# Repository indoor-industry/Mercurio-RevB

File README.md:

Requires CDFER's KiCAD library (https://github.com/CDFER/JLCPCB-Kicad-Library) and the custom symbol and footprint libraries in Component models/KiCAD_symbol_ library. 

Contains version with bare ESP32-S3R8 chip and version with ESP32-WROOM-1 module. Only major difference is bare chip version features RTC clock and uses strapping pin GPIO46 for ILI9341 DC line. This should work but has to be tested.

## License

See the [LICENSE](LICENSE) file for details.

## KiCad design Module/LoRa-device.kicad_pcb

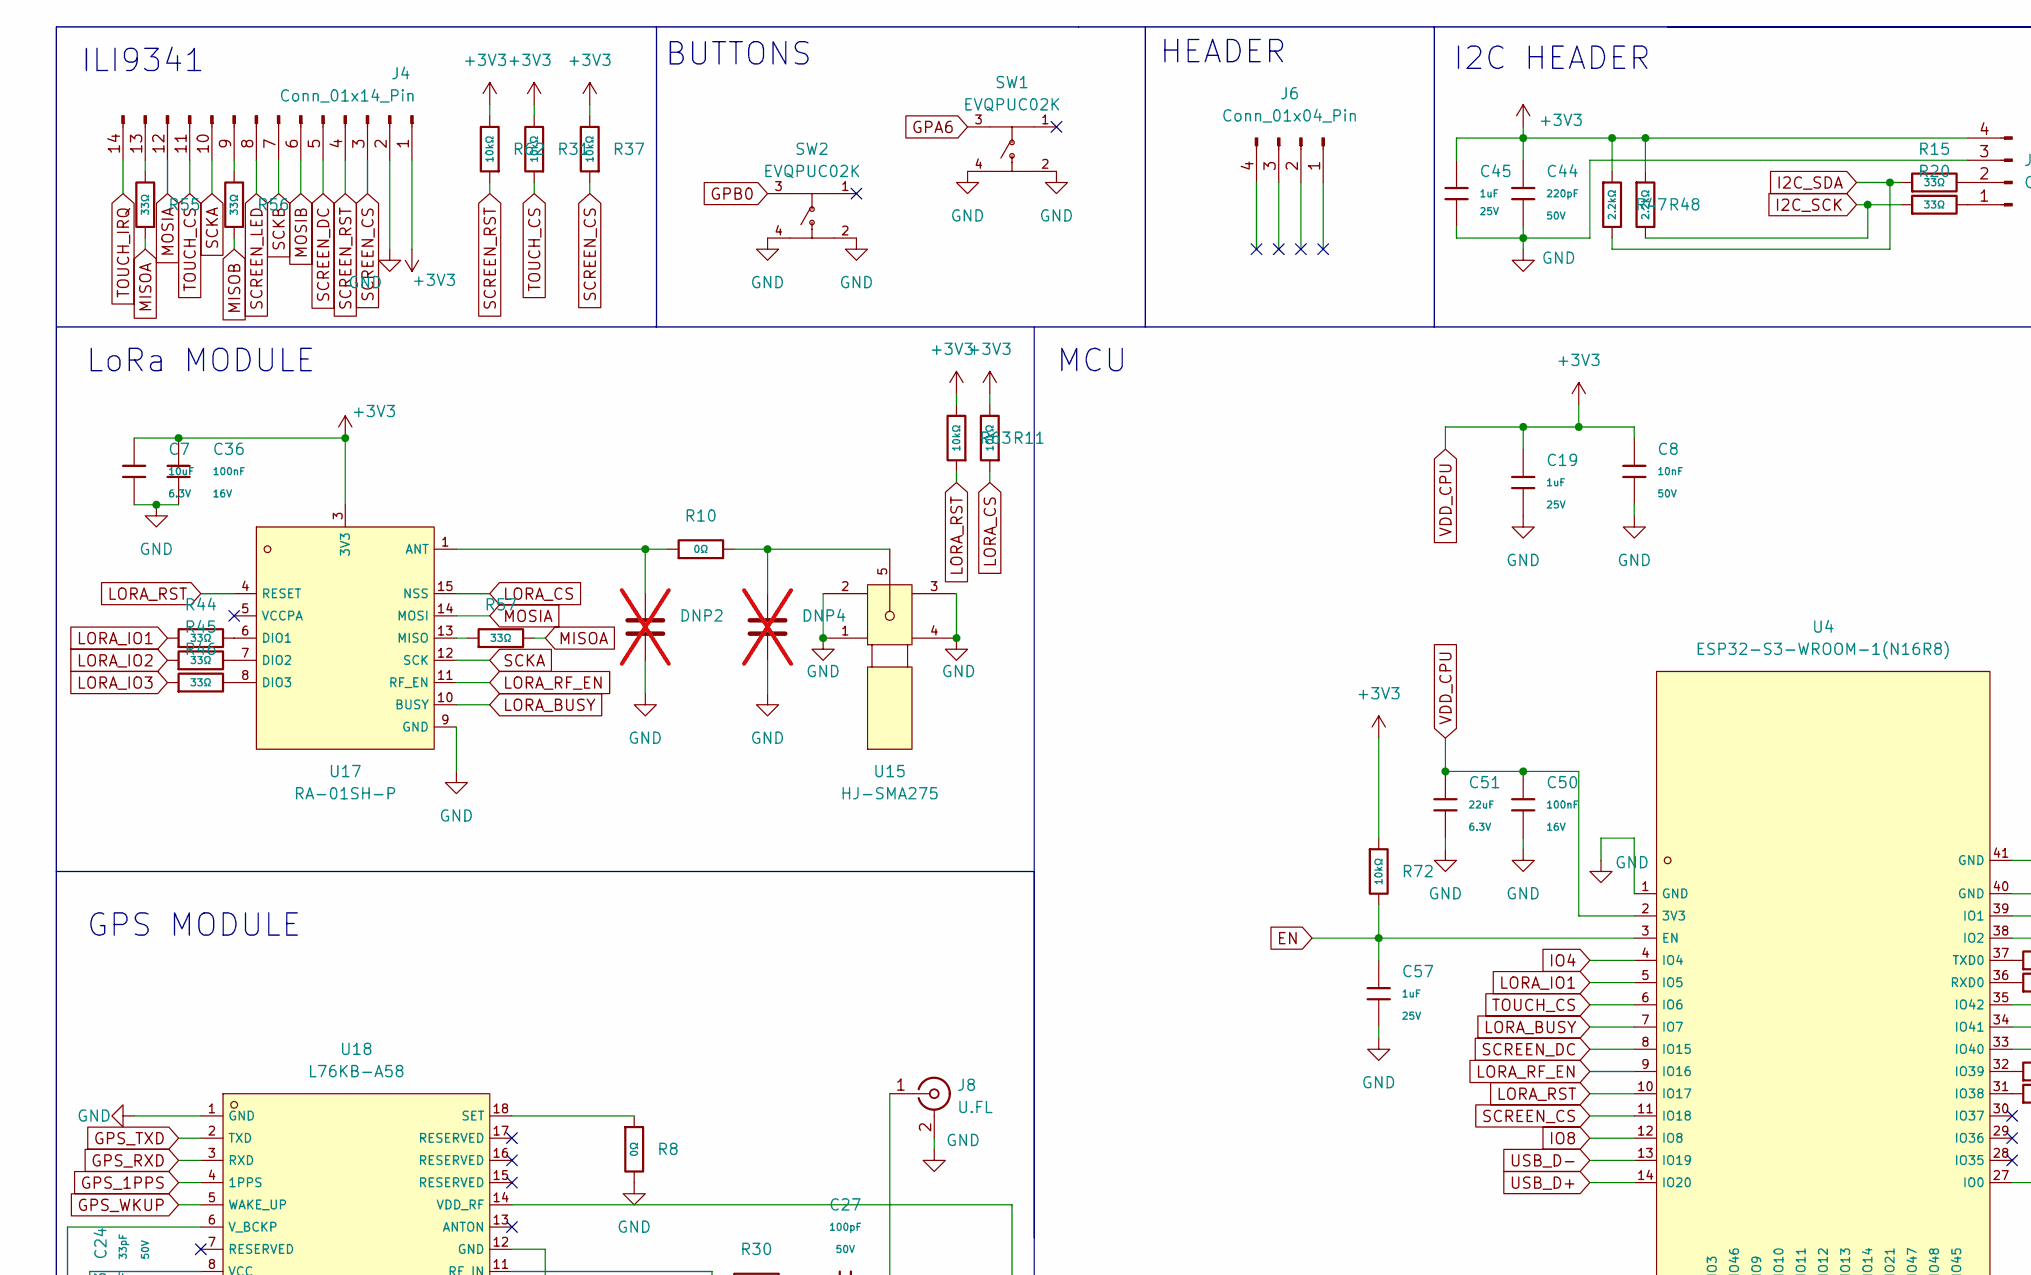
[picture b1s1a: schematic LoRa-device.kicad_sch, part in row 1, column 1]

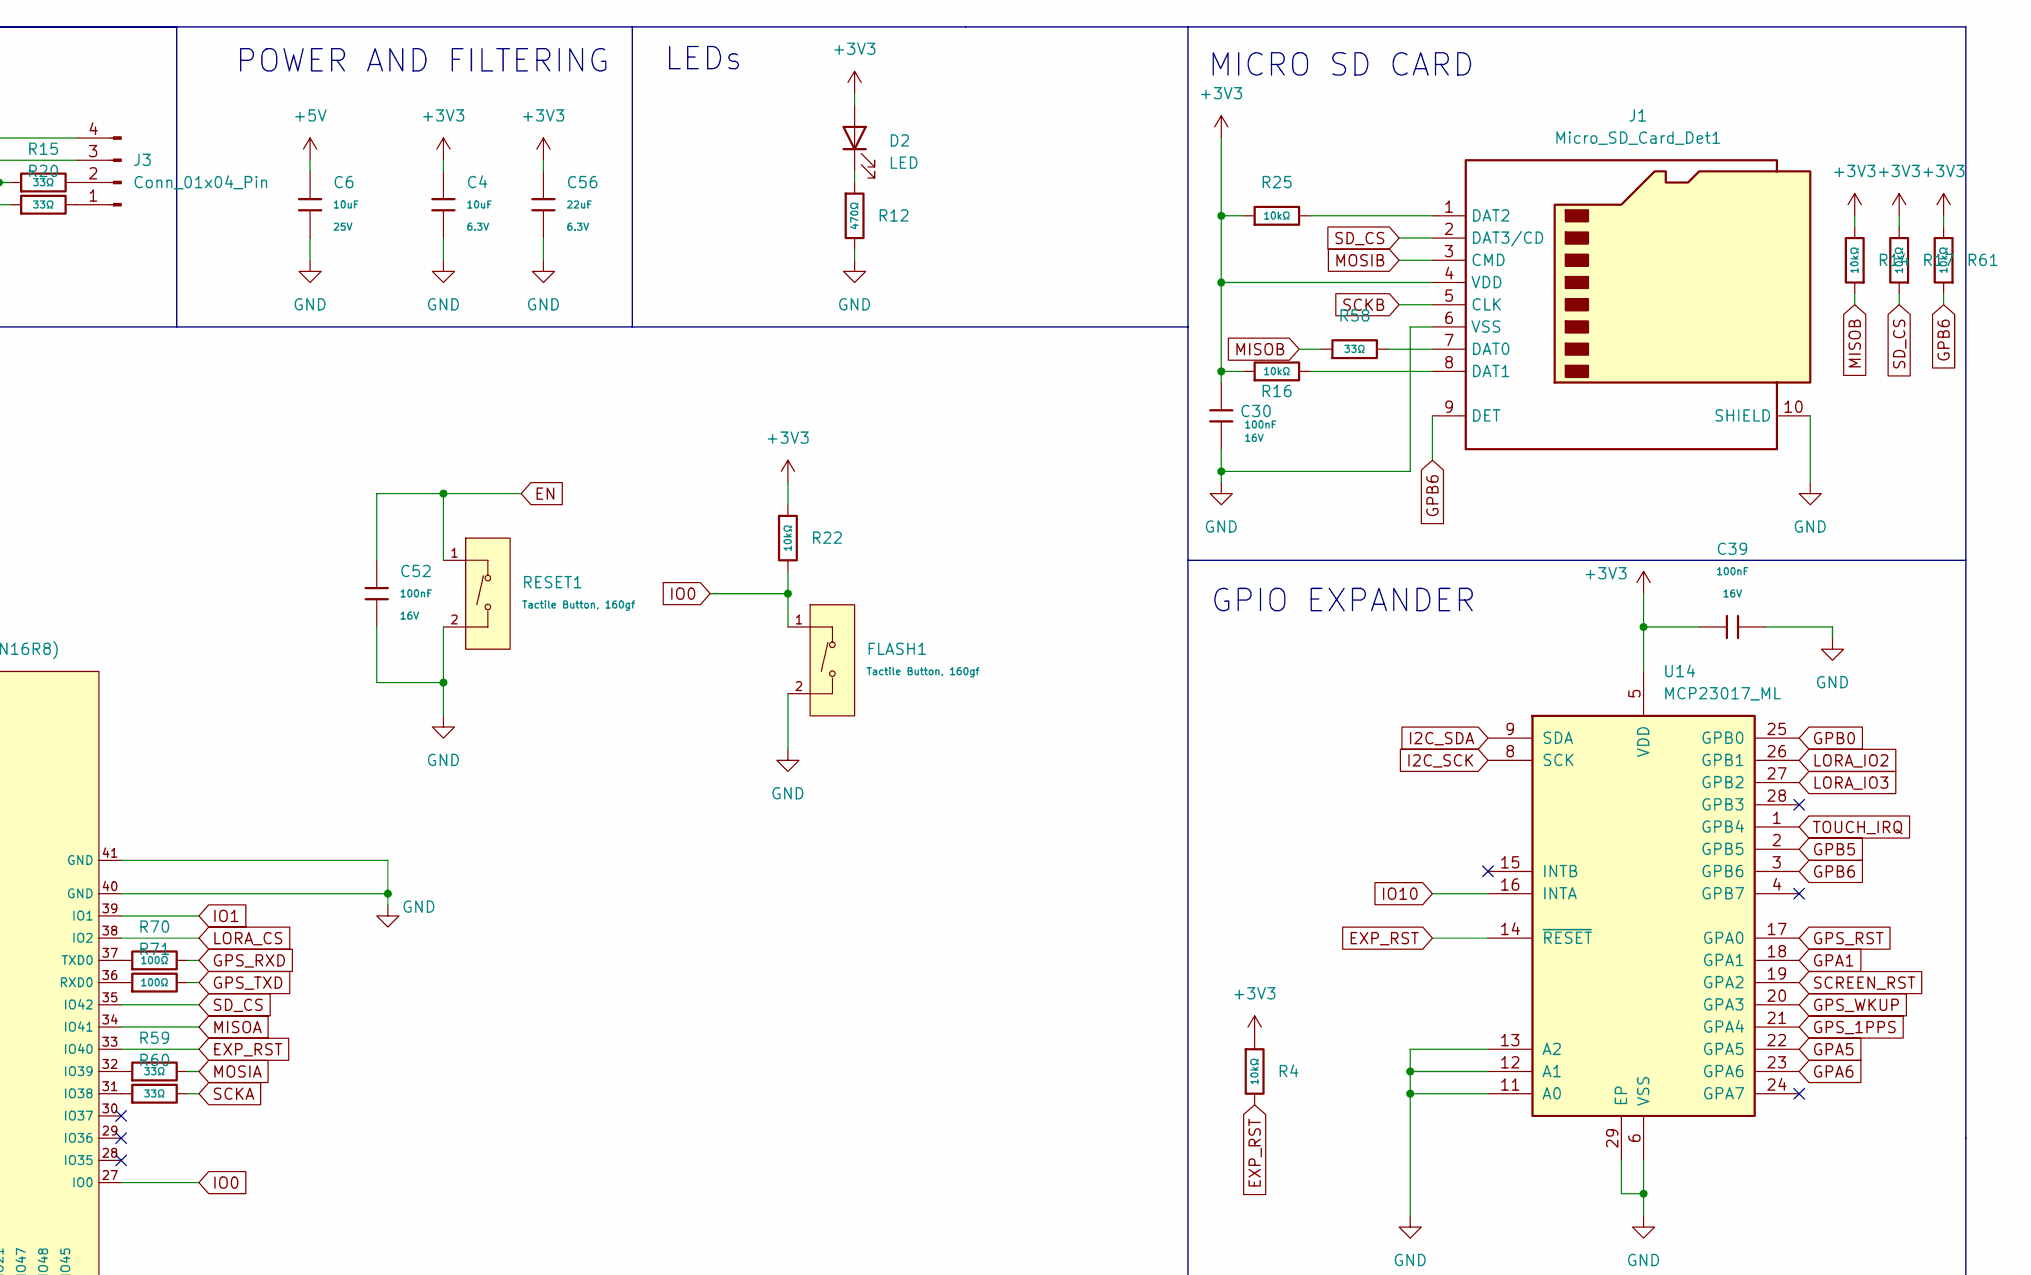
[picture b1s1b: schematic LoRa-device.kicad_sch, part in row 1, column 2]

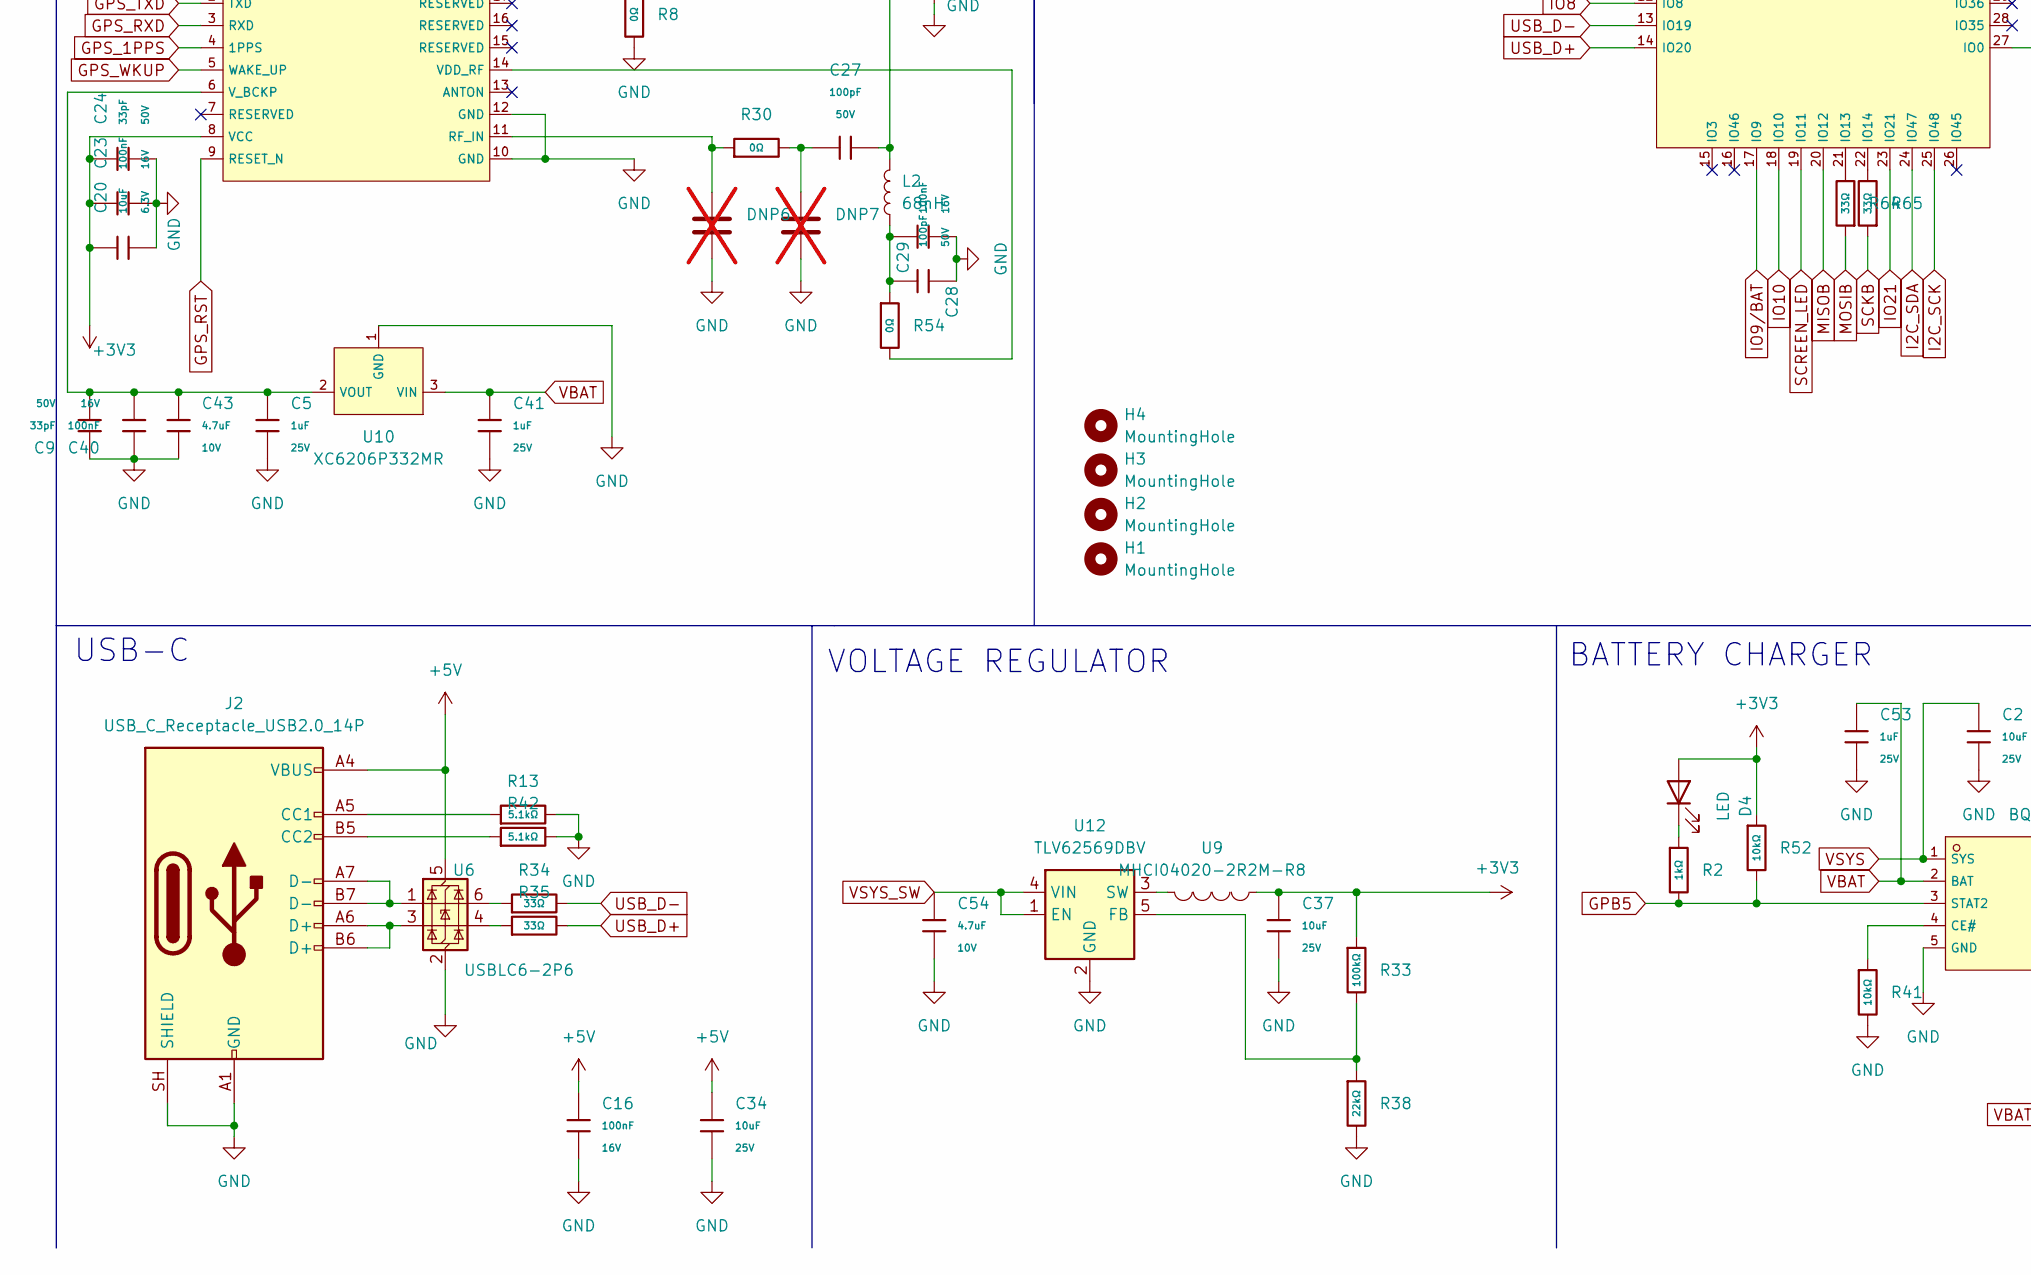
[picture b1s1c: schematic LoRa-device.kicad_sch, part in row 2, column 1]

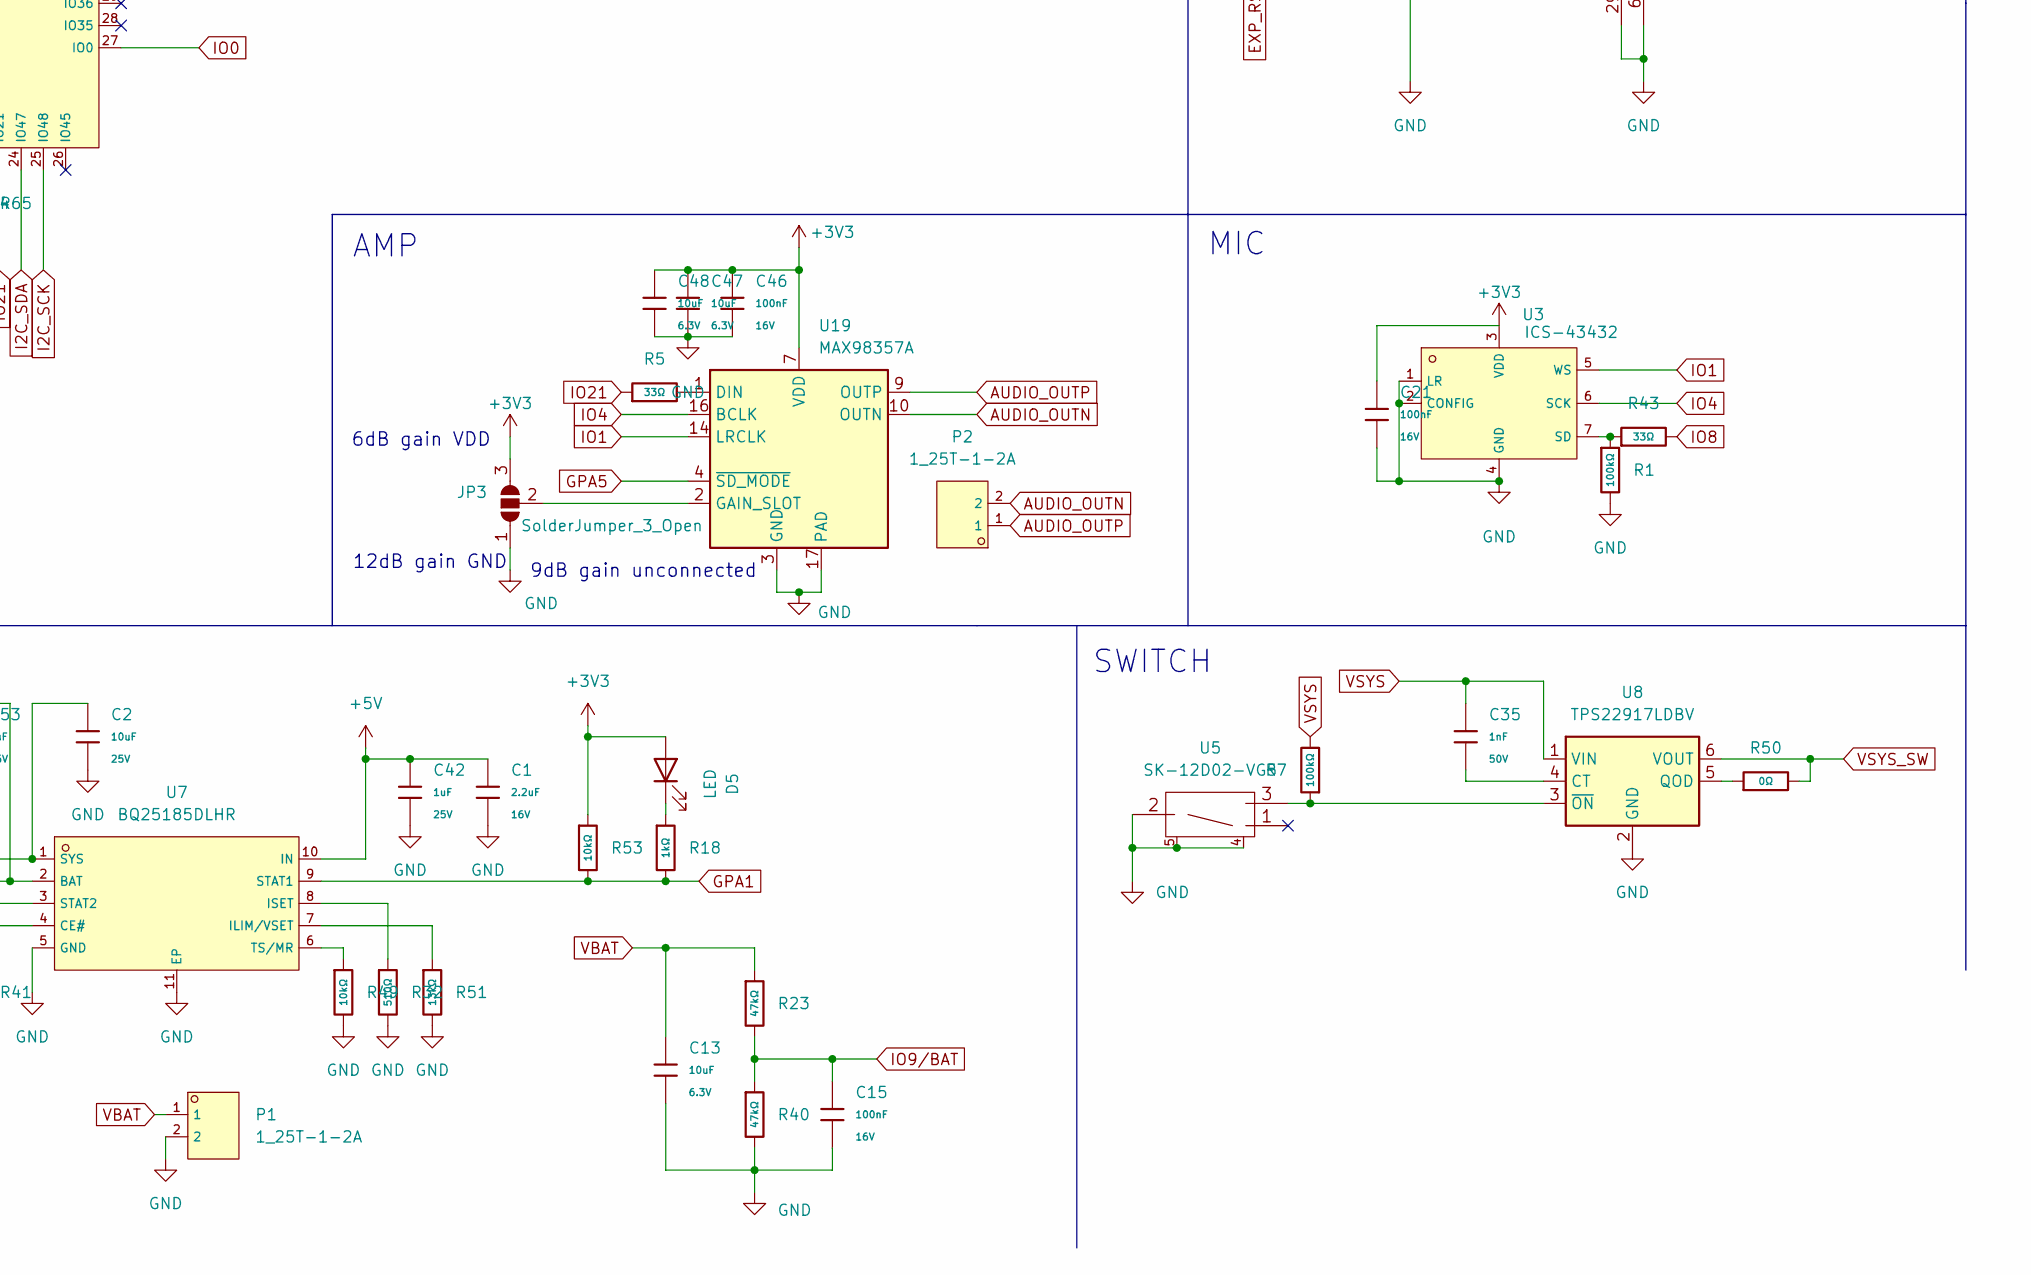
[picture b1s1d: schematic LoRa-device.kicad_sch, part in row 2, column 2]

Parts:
C1: 2.2uF; C_0603; Voltage Rated 16V; Tolerance ±10%; Part CL10A225KO8NNNC; LCSC C23630
C2, C6, C34, C37: 10uF; C_0603; Voltage Rated 25V; Tolerance ±20%; Part CL10A106MA8NRNC; LCSC C96446
C4, C7, C13, C20, C47, C48: 10uF; C_0402; Voltage Rated 6.3V; Tolerance ±20%; Part CL05A106MQ5NUNC; LCSC C15525
C5, C19, C41, C42, C45, C53, C57: 1uF; C_0402; Voltage Rated 25V; Tolerance ±10%; Part CL05A105KA5NQNC; LCSC C52923
C8: 10nF; C_0402; Voltage Rated 50V; Tolerance ±10%; Part CL05B103KB5NNNC; LCSC C15195
C9, C24: 33pF; C_0402; Voltage Rated 50V; Tolerance ±5%; Part 0402CG330J500NT; LCSC C1562
C15, C16, C21, C23, C29, C30, C36, C39, C40, C46, C50, C52: 100nF; C_0402; Voltage Rated 16V; Tolerance ±10%; Part CL05B104KO5NNNC; LCSC C1525
C27, C28: 100pF; C_0402; Voltage Rated 50V; Tolerance ±5%; Part 0402CG101J500NT; LCSC C1546
C35: 1nF; C_0402; Voltage Rated 50V; Tolerance ±10%; Part 0402B102K500NT; LCSC C1523
C43, C54: 4.7uF; C_0402; Voltage Rated 10V; Tolerance ±20%; Part CL05A475MP5NRNC; LCSC C23733
C44: 220pF; C_0402; Voltage Rated 50V; Tolerance ±10%; Part 0402B221K500NT; LCSC C1530
C51, C56: 22uF; C_0603; Voltage Rated 6.3V; Tolerance ±20%; Part CL10A226MQ8NRNC; LCSC C59461
D2, D4, D5: LED; LED_0603_1608Metric; Part KT-0603R; LCSC C2286
DNP2, DNP4, DNP6, DNP7: C_0402; not fitted
FLASH1: Tactile Button, 160gf; SW_TS-1088-AR02016; Voltage Rating (Dc) 12V; Part TS-1088-AR02016; LCSC C720477
H1, H2, H3, H4: MountingHole; MountingHole_3mm
J1: Micro_SD_Card_Det1; TF-SMD_TF-01A; Part TF-01A; LCSC C91145
J2: USB_C_Receptacle_USB2.0_14P; USB_C_Receptacle_HCTL_HC-TYPE-C-16P-01A; Part HC-TYPE-C-16P-3M2S; LCSC C19274016
J3, J6: Conn_01x04_Pin; PinSocket_1x04_P2.54mm_Vertical
J4: Conn_01x14_Pin; PinSocket_1x14_P2.54mm_Vertical
J8: U.FL; IPEX-SMD_BWIPX-1-001E; Part BWU.FL-IPEX1; LCSC C5137195
JP3: SolderJumper_3_Open; SolderJumper-3_P1.3mm_Open_RoundedPad1.0x1.5mm
L2: 68nH; L_0402; Part SDCL1005C68NJTDF; LCSC C32836
P1, P2: 1_25T-1-2A; CONN-TH_1.25T-1-2A; LCSC C10819
R1, R7, R33: 100kΩ; R_0402; Overload Voltage (Max) 50V; Tolerance ±1%; Part 0402WGF1003TCE; LCSC C25741
R2, R18: 1kΩ; R_0402; Overload Voltage (Max) 50V; Tolerance ±1%; Part 0402WGF1001TCE; LCSC C11702
R4, R11, R14, R16, R17, R22, R25, R31, R37, R41, R49, R52, R53, R61, R62, R63, R72: 10kΩ; R_0402; Overload Voltage (Max) 50V; Tolerance ±1%; Part 0402WGF1002TCE; LCSC C25744
R5, R15, R20, R34, R35, R43, R44, R45, R46, R55, R56, R57, R58, R59, R60, R64, R65: 33Ω; R_0402; Overload Voltage (Max) 50V; Tolerance ±1%; Part 0402WGF330JTCE; LCSC C25105
R8, R10, R30, R50, R54: 0Ω; R_0402; Overload Voltage (Max) 50V; Tolerance ±1%; Part 0402WGF0000TCE; LCSC C17168
R12: 470Ω; R_0402; Overload Voltage (Max) 50V; Tolerance ±1%; Part 0402WGF4700TCE; LCSC C25117
R13, R42: 5.1kΩ; R_0402; Overload Voltage (Max) 50V; Tolerance ±1%; Part 0402WGF5101TCE; LCSC C25905
R23, R40: 47kΩ; R_0402; Overload Voltage (Max) 50V; Tolerance ±1%; Part 0402WGF4702TCE; LCSC C25792
R32: 510Ω; R_0402; Overload Voltage (Max) 50V; Tolerance ±1%; Part 0402WGF5100TCE; LCSC C25123
R38: 22kΩ; R_0402; Overload Voltage (Max) 50V; Tolerance ±1%; Part 0402WGF2202TCE; LCSC C25768
R47, R48: 2.2kΩ; R_0402; Overload Voltage (Max) 50V; Tolerance ±1%; Part 0402WGF2201TCE; LCSC C25879
R51: 13kΩ; R_0603; Overload Voltage (Max) 75V; Tolerance ±1%; Part 0603WAF1302T5E; LCSC C22797
R70, R71: 100Ω; R_0402; Overload Voltage (Max) 50V; Tolerance ±1%; Part 0402WGF1000TCE; LCSC C25076
RESET1: Tactile Button, 160gf; SW_TS-1088-AR02016; Voltage Rating (Dc) 12V; Part TS-1088-AR02016; LCSC C720477
SW1, SW2: EVQPUC02K; SW-SMD_EVQPUD02K; Part EVQPUC02K; LCSC C79174
U3: ICS-43432; SENSOR-SMD_ICS-43432; Part ICS-43432; LCSC C574021
U4: ESP32-S3-WROOM-1(N16R8); WIRELM-SMD_ESP32-S3-WROOM-1; Part ESP32-S3-WROOM-1(N16R8); LCSC C2913202
U5: SK-12D02-VG5; SW-TH_SK-12D02-VG5; Part SK-12D02-VG5; LCSC C136722
U6: USBLC6-2P6; SOT-666; Part USBLC6-2P6; LCSC C15999
U7: BQ25185DLHR; WSON-10_L2.2-W2.0-P0.40-BL-EP_TI_DLH0010A; Part BQ25185DLHR; LCSC C19725033
U8: TPS22917LDBV; SOT-23-6; Part TPS22917LDBVR; LCSC C3235537
U9: MHCI04020-2R2M-R8; IND-SMD_L4.6-W4.1; Part MHCI04020-2R2M-R8; LCSC C142096
U10: XC6206P332MR; SOT-23-3_L2.9-W1.6-P1.90-LS2.8-BR; Output Voltage 3.3V; Dropout Voltage 680mV@(100mA); Part XC6206P332MR-G; LCSC C5446
U12: TLV62569DBV; SOT-23-5; Part TLV62569DBVR; LCSC C141836
U14: MCP23017_ML; QFN-28-1EP_6x6mm_P0.65mm_EP4.25x4.25mm; Part MCP23017T-E/ML; LCSC C629439
U15: HJ-SMA275; SMA-SMD_BWSMA-KE-P001; Part HJ-SMA275; LCSC C2693809
U17: RA-01SH-P; COMM-SMD_17P-L17.0-W16.0-P2.00_RA-01S-P; Part Ra-01SH-P; LCSC C42420049
U18: L76KB-A58; GPSM-SMD_18P-L10.1-W9.7-P1.10; Part L76KB-A58; LCSC C2916234
U19: MAX98357A; TQFN-16-1EP_3x3mm_P0.5mm_EP1.23x1.23mm; Part MAX98357AETE+T; LCSC C910544

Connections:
+5V: C1.1, C6.1, C16.1, C34.1, C42.1, J2.A4 (VBUS), J2.A9 (VBUS), J2.B4 (VBUS), J2.B9 (VBUS), U6.5 (VBUS), U7.10 (IN)
AUDIO_OUTN: P2.2, U19.10 (OUTN)
AUDIO_OUTP: P2.1, U19.9 (OUTP)
EN: C52.1, C57.1, R72.2, RESET1.1 (A), U4.3 (EN)
EXP_RST: R4.2, U4.33 (IO40), U14.14 (~RESET)
GND: C1.2, C2.2, C4.2, C5.2, C6.2, C7.2, C8.2, C9.1, C13.2, C15.2, C16.2, C19.2, C20.2, C21.2, C23.2, C24.2, C28.2, C29.2, C30.2, C34.2, C36.2, C37.2, C39.1, C40.1, C41.2, C42.2, C43.2, C44.2, C45.2, C46.2, C47.2, C48.2, C50.1, C51.2, C52.2, C53.2, C54.2, C56.2, C57.2, DNP2.2, DNP4.2, DNP6.2, DNP7.2, FLASH1.2 (B), J1.6 (VSS), J1.10 (SHIELD), J1.11 (SHIELD), J1.12 (SHIELD), J1.13 (SHIELD), J2.A1 (GND), J2.A12 (GND), J2.B1 (GND), J2.B12 (GND), J2.SH (SHIELD), J3.3, J4.2, J8.2 (Ext), J8.3 (Ext), JP3.1 (A), P1.2, R1.2, R8.2, R12.2, R13.2, R32.2, R38.2, R40.2, R41.2, R42.2, R49.2, R51.2, RESET1.2 (B), SW1.2, SW1.4, SW2.2, SW2.4, U3.1 (LR), U3.2 (CONFIG), U3.4 (GND), U4.1 (GND), U4.40 (GND), U4.41 (GND), U5.2, U5.4, U5.5, U6.2 (GND), U7.5 (GND), U7.11 (EP), U8.2 (GND), U10.1 (GND), U12.2 (GND), U14.6 (VSS), U14.11 (A0), U14.12 (A1), U14.13 (A2), U14.29 (EP), U15.1, U15.2, U15.3, U15.4, U17.2 (GND), U17.9 (GND), U17.16 (GND), U17.17 (GND), U18.1 (GND), U18.10 (GND), U18.12 (GND), U19.3 (GND), U19.11 (GND), U19.15 (GND), U19.17 (PAD)
GPA1: R18.2, R53.2, U7.9 (STAT1), U14.18 (GPA1)
GPA5: U14.22 (GPA5), U19.4 (~SD_MODE)
GPA6: SW1.3, U14.23 (GPA6)
GPB0: SW2.3, U14.25 (GPB0)
GPB5: R2.2, R52.2, U7.3 (STAT2), U14.2 (GPB5)
GPB6: J1.9 (DET), R61.1, U14.3 (GPB6)
GPS_1PPS: U14.21 (GPA4), U18.4 (1PPS)
GPS_RST: U14.17 (GPA0), U18.9 (RESET_N)
GPS_RXD: R70.2, U18.3 (RXD)
GPS_TXD: R71.2, U18.2 (TXD)
GPS_WKUP: U14.20 (GPA3), U18.5 (WAKE_UP)
I2C_SCK: R20.1, R48.2, U4.25 (IO48), U14.8 (SCK)
I2C_SDA: R15.1, R47.2, U4.24 (IO47), U14.9 (SDA)
IO0: FLASH1.1 (A), R22.2, U4.27 (IO0)
IO1: U3.5 (WS), U4.39 (IO1), U19.14 (LRCLK)
IO4: U3.6 (SCK), U4.4 (IO4), U19.16 (BCLK)
IO8: R43.2, U4.12 (IO8)
IO9/BAT: C15.1, R23.2, R40.1, U4.17 (IO9)
IO10: U4.18 (IO10), U14.16 (INTA)
IO21: R5.1, U4.23 (IO21)
LORA_BUSY: U4.7 (IO7), U17.10 (BUSY)
LORA_CS: R11.1, U4.38 (IO2), U17.15 (NSS)
LORA_IO1: R44.1, U4.5 (IO5)
LORA_IO2: R45.1, U14.26 (GPB1)
LORA_IO3: R46.1, U14.27 (GPB2)
LORA_RF_EN: U4.9 (IO16), U17.11 (RF_EN)
LORA_RST: R63.1, U4.10 (IO17), U17.4 (RESET)
MISOA: R55.1, R57.2, U4.34 (IO41)
MISOB: R14.1, R56.1, R58.1, U4.20 (IO12)
MOSIA: J4.12, R59.2, U17.14 (MOSI)
MOSIB: J1.3 (CMD), J4.6, R64.1
unnamed: C27.1, DNP7.1, R30.2
unnamed: C28.1, C29.1, L2.1, R54.1
unnamed: D2.1 (K), R12.1
unnamed: D4.1 (K), R2.1
unnamed: D5.1 (K), R18.1
unnamed: DNP4.1, R10.2, U15.5
unnamed: J1.7 (DAT0), R58.2
unnamed: J1.8 (DAT1), R16.2
unnamed: J1.1 (DAT2), R25.2
unnamed: J2.A5 (CC1), R13.1
unnamed: J2.B5 (CC2), R42.1
unnamed: J2.A6 (D+), J2.B6 (D+), U6.3 (I/O2)
unnamed: J2.A7 (D-), J2.B7 (D-), U6.1 (I/O1)
unnamed: J3.1, R20.2
unnamed: J3.2, R15.2
unnamed: J4.9, R56.2
unnamed: J4.13, R55.2
unnamed: C27.2, J8.1 (In), L2.2
unnamed: JP3.2 (C), U19.2 (GAIN_SLOT)
unnamed: R34.1, U6.6 (I/O1)
unnamed: R35.1, U6.4 (I/O2)
unnamed: R1.1, R43.1, U3.7 (SD)
unnamed: R64.2, U4.21 (IO13)
unnamed: R65.2, U4.22 (IO14)
unnamed: R60.1, U4.31 (IO38)
unnamed: R59.1, U4.32 (IO39)
unnamed: R71.1, U4.36 (RXD0)
unnamed: R70.1, U4.37 (TXD0)
unnamed: R41.1, U7.4 (CE#)
unnamed: R51.1, U7.7 (ILIM/VSET)
unnamed: R32.1, U7.8 (ISET)
unnamed: R49.1, U7.6 (TS/MR)
unnamed: C35.2, U8.4 (CT)
unnamed: R50.1, U8.5 (QOD)
unnamed: R7.1, U5.3, U8.3 (~ON)
unnamed: C5.1, C9.2, C40.2, C43.1, U10.2 (VOUT), U18.6 (V_BCKP)
unnamed: R33.2, R38.1, U12.5 (FB)
unnamed: U9.1, U12.3 (SW)
unnamed: DNP2.1, R10.1, U17.1 (ANT)
unnamed: R44.2, U17.6 (DIO1)
unnamed: R45.2, U17.7 (DIO2)
unnamed: R46.2, U17.8 (DIO3)
unnamed: R57.1, U17.13 (MISO)
unnamed: DNP6.1, R30.1, U18.11 (RF_IN)
unnamed: R8.1, U18.18 (SET)
unnamed: R54.2, U18.14 (VDD_RF)
unnamed: R5.2, U19.1 (DIN)
SCKA: J4.10, R60.2, U17.12 (SCK)
SCKB: J1.5 (CLK), J4.7, R65.1
SCREEN_CS: J4.3, R37.1, U4.11 (IO18)
SCREEN_DC: J4.5, U4.8 (IO15)
SCREEN_LED: J4.8, U4.19 (IO11)
SCREEN_RST: J4.4, R62.1, U14.19 (GPA2)
SD_CS: J1.2 (DAT3/CD), R17.1, U4.35 (IO42)
TOUCH_CS: J4.11, R31.1, U4.6 (IO6)
TOUCH_IRQ: J4.14, U14.1 (GPB4)
USB_D+: R35.2, U4.14 (IO20)
USB_D-: R34.2, U4.13 (IO19)
VBAT: C13.1, C41.1, C53.1, P1.1, R23.1, U7.2 (BAT), U10.3 (VIN)
VDD_CPU: C4.1, C7.1, C8.1, C19.1, C20.1, C21.1, C23.1, C24.1, C30.1, C36.1, C37.1, C39.2, C44.1, C45.1, C46.1, C47.1, C48.1, C50.2, C51.1, C56.1, D2.2 (A), D4.2 (A), D5.2 (A), J1.4 (VDD), J3.4, J4.1, JP3.3 (B), R4.1, R11.2, R14.2, R16.1, R17.2, R22.1, R25.1, R31.2, R33.1, R37.2, R47.1, R48.1, R52.1, R53.1, R61.2, R62.2, R63.2, R72.1, U3.3 (VDD), U4.2 (3V3), U9.2, U14.5 (VDD), U17.3 (3V3), U18.8 (VCC), U19.7 (VDD), U19.8 (VDD)
VSYS: C2.1, C35.1, R7.2, U7.1 (SYS), U8.1 (VIN)
VSYS_SW: C54.1, R50.2, U8.6 (VOUT), U12.1 (EN), U12.4 (VIN)

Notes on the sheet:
BATTERY CHARGER
VOLTAGE REGULATOR
MIC
LoRa MODULE
LEDs
MCU
HEADER
MICRO SD CARD
GPS MODULE
AMP
I2C HEADER
ILI9341
9dB gain unconnected
SWITCH
12dB gain GND
6dB gain VDD
POWER AND FILTERING
BUTTONS
USB-C
GPIO EXPANDER

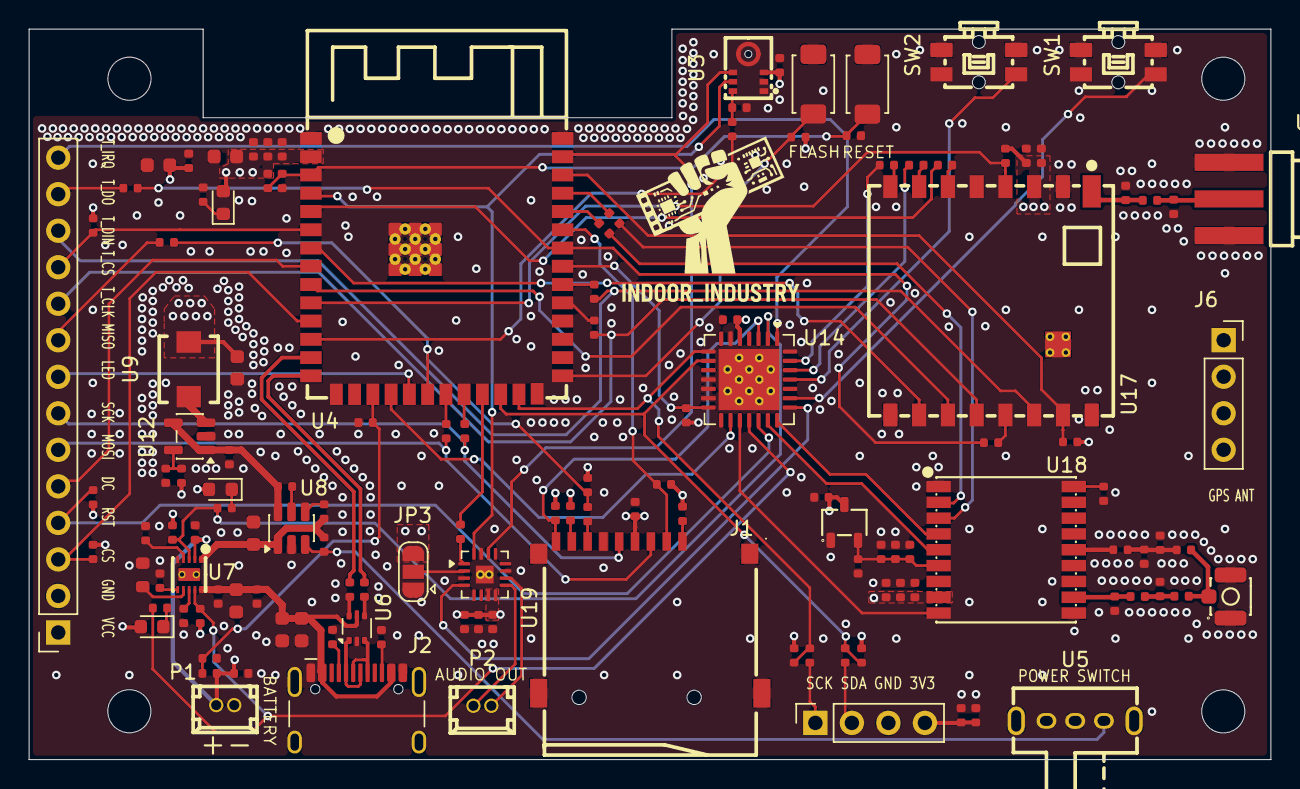
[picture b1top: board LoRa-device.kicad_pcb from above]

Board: 4 copper layers, 86.4 x 50.8 mm, 136 parts (0 on the bottom side), 99 nets.

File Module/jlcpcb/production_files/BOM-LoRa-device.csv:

Comment,Designator,Footprint,LCSC,Quantity
0Ω,"R10,R30,R50,R54,R8",R_0402,C17168,5
100kΩ,"R1,R33,R7",R_0402,C25741,3
100nF,"C15,C16,C21,C23,C29,C30,C36,C39,C40,C46,C50,C52",C_0402,C1525,12
100pF,"C27,C28",C_0402,C1546,2
100Ω,"R70,R71",R_0402,C25076,2
10kΩ,"R11,R14,R16,R17,R22,R25,R31,R37,R4,R41,R49,R52,R53,R61,R62,R63,R72",R_0402,C25744,17
10nF,C8,C_0402,C15195,1
10uF,"C13,C20,C4,C47,C48,C7",C_0402,C15525,6
10uF,"C2,C34,C37,C6",C_0603,C96446,4
13kΩ,R51,R_0603,C22797,1
1kΩ,"R18,R2",R_0402,C11702,2
1nF,C35,C_0402,C1523,1
1uF,"C19,C41,C42,C45,C5,C53,C57",C_0402,C52923,7
2.2kΩ,"R47,R48",R_0402,C25879,2
2.2uF,C1,C_0603,C23630,1
220pF,C44,C_0402,C1530,1
22kΩ,R38,R_0402,C25768,1
22uF,"C51,C56",C_0603,C59461,2
33pF,"C24,C9",C_0402,C1562,2
33Ω,"R15,R20,R34,R35,R43,R44,R45,R46,R5,R55,R56,R57,R58,R59,R60,R64,R65",R_0402,C25105,17
4.7uF,"C43,C54",C_0402,C23733,2
470Ω,R12,R_0402,C25117,1
47kΩ,"R23,R40",R_0402,C25792,2
5.1kΩ,"R13,R42",R_0402,C25905,2
510Ω,R32,R_0402,C25123,1
68nH,L2,L_0402,C32836,1
BQ25185DLHR,U7,WSON-10_L2.2-W2.0-P0.40-BL-EP_TI_DLH0010A,C19725033,1
ESP32-S3-WROOM-1(N16R8),U4,WIRELM-SMD_ESP32-S3-WROOM-1,C2913202,1
EVQPUC02K,"SW1,SW2",SW-SMD_EVQPUD02K,C79174,2
ICS-43432,U3,SENSOR-SMD_ICS-43432,C574021,1
L76KB-A58,U18,GPSM-SMD_18P-L10.1-W9.7-P1.10,C2916234,1
LED,"D2,D4,D5",LED_0603_1608Metric,C2286,3
MAX98357A,U19,TQFN-16-1EP_3x3mm_P0.5mm_EP1.23x1.23mm,C910544,1
MCP23017_ML,U14,QFN-28-1EP_6x6mm_P0.65mm_EP4.25x4.25mm,C629439,1
MHCI04020-2R2M-R8,U9,IND-SMD_L4.6-W4.1,C142096,1
Micro_SD_Card_Det1,J1,TF-SMD_TF-01A,C91145,1
RA-01SH-P,U17,COMM-SMD_17P-L17.0-W16.0-P2.00_RA-01S-P,C42420049,1
SK-12D02-VG5,U5,SW-TH_SK-12D02-VG5,C136722,1
TLV62569DBV,U12,SOT-23-5,C141836,1
TPS22917LDBV,U8,SOT-23-6,C3235537,1
"Tactile Button, 160gf","FLASH1,RESET1",SW_TS-1088-AR02016,C720477,2
U.FL,J8,IPEX-SMD_BWIPX-1-001E,C5137195,1
USBLC6-2P6,U6,SOT-666,C15999,1
USB_C_Receptacle_USB2.0_14P,J2,USB_C_Receptacle_HCTL_HC-TYPE-C-16P-01A,C19274016,1
XC6206P332MR,U10,SOT-23-3_L2.9-W1.6-P1.90-LS2.8-BR,C5446,1

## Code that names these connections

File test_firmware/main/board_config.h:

#pragma once

/*
 * LoRa Device RevB — board pin map, register/bitmask defines, and shared
 * UI constants. Included by every driver module and the test framework.
 *
 * SPI-A (SPI2) SCLK=38 MOSI=39 MISO=41 → LoRa SX1262 CS=2, Touch XPT2046 CS=6
 * SPI-B (SPI3) SCLK=14 MOSI=13 MISO=12 → ILI9341 CS=18 DC=15 LED=11, SD CS=42
 * I2C0 SDA=47 SCL=48 → MCP23017 0x20 (RST=GPIO40)
 *   GPA: 0=GPS_RST 1=STAT1(in) 2=DISP_RST 3=GPS_WKUP 4=GPS_1PPS(in) 5=AUD_EN 6=SW1(in)
 *   GPB: 0=SW2(in) 1=LORA_IO2(in) 2=LORA_IO3(in) 4=TOUCH_IRQ(in) 5=STAT2(in) 6=SD_DET(in)
 * I2S0: BCLK=4 LRCLK=1 DOUT=21(MAX98357A) DIN=8(ICS-43432)
 * UART1: GPS L76KB TX=43 RX=44 9600baud
 * ADC1ch8 GPIO9: battery (Vpin=Vbat/2, R=47k/47k)
 */

#include "driver/spi_master.h"
#include "esp_adc/adc_oneshot.h"
#include "driver/uart.h"

/* =========================================================================
 * Hardware pins
 * ========================================================================= */
#define SPI_A_HOST   SPI2_HOST
#define PIN_LORA_SCLK 38
#define PIN_LORA_MOSI 39
#define PIN_LORA_MISO 41
#define PIN_LORA_CS   2
#define PIN_LORA_RST  17
#define PIN_LORA_BUSY 7
#define PIN_LORA_DIO1 5
#define PIN_LORA_RFEN 16
#define PIN_TOUCH_CS  6

#define SPI_B_HOST    SPI3_HOST
#define PIN_DISP_SCLK 14
#define PIN_DISP_MOSI 13
#define PIN_DISP_MISO 12
#define PIN_DISP_CS   18
#define PIN_DISP_DC   15
#define PIN_DISP_LED  11
#define PIN_SD_CS     42

#define PIN_I2C_SDA   47
#define PIN_I2C_SCL   48
#define MCP_ADDR      0x20
#define PIN_EXP_RST   40
#define PIN_EXP_INTA  10

#define PIN_I2S_BCLK  4
#define PIN_I2S_LRCLK 1
#define PIN_I2S_DOUT  21
#define PIN_I2S_DIN   8

#define GPS_UART      UART_NUM_1
#define PIN_GPS_TX    43
#define PIN_GPS_RX    44

#define BAT_ADC_UNIT  ADC_UNIT_1
#define BAT_ADC_CHAN  ADC_CHANNEL_8

#define PIN_BOOT_BTN  0

/* MCP23017 register addresses */
#define MCP_IODIRA 0x00
#define MCP_IODIRB 0x01
#define MCP_GPPUA  0x0C
#define MCP_GPPUB  0x0D
#define MCP_GPIOA  0x12
#define MCP_GPIOB  0x13
#define MCP_OLATA  0x14
#define MCP_OLATB  0x15

/* MCP23017 bit masks */
#define GPA_GPS_RST    (1u<<0)
#define GPA_STAT1      (1u<<1)
#define GPA_DISP_RST   (1u<<2)
#define GPA_GPS_WKUP   (1u<<3)
#define GPA_GPS_1PPS   (1u<<4)
#define GPA_AUDIO_EN   (1u<<5)
#define GPA_SW1        (1u<<6)

#define GPB_SW2        (1u<<0)
#define GPB_LORA_IO2   (1u<<1)
#define GPB_LORA_IO3   (1u<<2)
#define GPB_TOUCH_IRQ  (1u<<4)
#define GPB_STAT2      (1u<<5)
#define GPB_SD_DET     (1u<<6)

/* Screen */
#define SCR_W 240
#define SCR_H 320

#define RGB565(r,g,b) ((uint16_t)((((r)&0xF8)<<8)|(((g)&0xFC)<<3)|(((b)&0xF8)>>3)))
#define C_BLACK  RGB565(  0,  0,  0)
#define C_WHITE  RGB565(255,255,255)
#define C_RED    RGB565(220, 40, 40)
#define C_GREEN  RGB565( 40,200, 40)
#define C_BLUE   RGB565( 30, 80,200)
#define C_ORANGE RGB565(255,140,  0)
#define C_YELLOW RGB565(255,220,  0)
#define C_GRAY   RGB565( 80, 80, 80)
#define C_DGRAY  RGB565( 25, 25, 25)
#define C_TEAL   RGB565(  0,155,155)
#define C_NAVY   RGB565(  0, 40,100)
#define C_VIOLET RGB565(120,  0,180)

/* UI layout */
#define HDR_H     28   /* main/detail header height */
#define DROW_H    14   /* detail content row height (scale-1 text + margin) */
#define DPAD       4   /* left text margin */
#define DCONTENT_Y HDR_H  /* content area starts here */

/* Test indices (must match g_tests order) */
#define IDX_SYSTEM  0
#define IDX_BATTERY 1
#define IDX_MCP     2
#define IDX_LORA    3
#define IDX_SD      4
#define IDX_GPS     5
#define IDX_MIC     6
#define IDX_SPEAKER 7
#define IDX_TOUCH   8
#define IDX_WIFI    9

/* Main-menu layout */
#define MAIN_ROW_H  26
#define BADGE_W     64
#define RUNALL_Y    (HDR_H + 10 * MAIN_ROW_H)
#define RUNALL_H    (SCR_H - RUNALL_Y)

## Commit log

2026-03-16 Major overhaul of version A
2026-03-17 Just a backup.
2026-03-26 Cleanup and update project files.
2026-03-30 Backing up.
2026-03-31 To be routed, most work likely done.
2026-04-03 new case design.
2026-04-05 progress
2026-04-06 Changed problematic components, updated case
2026-04-08 Added buttons to case, rehauled power supply.
2026-04-09 Almost ready for routing, major fixes, case ready.
2026-04-13 Case prototype ready. Added thermal pads.
2026-04-14 Ready for routing!
2026-04-15 Minor layout changes
2026-04-16 Routing started
2026-04-17 More routing, modifying case buttons and locking
2026-04-20 Modified case and progressed routing
2026-04-24 Solved DRCs, updated case model
2026-04-26 Minor component changes.
2026-04-29 Perfected 3V3 routing
2026-05-03 Production ready prototype
2026-05-10 Added version with module for easier cert
2026-05-11 Revised production ready bare chip and module ver.
2026-05-14 This version has been sent to production.
2026-06-10 First peripheral test firmware
2026-06-14 test_firmware works clean
2026-06-16 Serial monitor now works. Custom board defined.
